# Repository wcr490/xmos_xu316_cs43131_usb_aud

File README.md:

# xmos_xu316_cs43131_usb_aud

## Firmware Compilation Steps

* install xmos xtc tools vscode extension
* clone (https://github.com/youheng7185/sw_usb_audio.git)
* open with vscode, try building
* after getting error from lib_board_support, delete the lib_board_support and clone this (https://github.com/youheng7185/lib_board_support) into that directory
* when build finishes, run ```./pack.sh``` to generate the rom for qspi flash
* flash qspi flash with ```output.bin```

## Reference

* Bric for its cs43131 schematics and init sequence (https://github.com/zephray/Bric)
* Blog by WuXi for cs43131 registers (https://wuxiproj.mzy7.cn/posts/a75c0c32)

## Main Component
* XU316-1024-QF60B-C24
* STMicro USB6B1 USB ESD protection
* Generic USB-C 2.0 TH port
* Winbond W25Q64JVS
* Seiko Epson FA-238 (24 Mhz)
* TI TPS563201 (1.8v dcdc), this requires a 252012 size 2.2uH inductor
* RT9013-33GB, 3.3v ldo
* RT9013-18GB, 1.8v ldo (x4, notes: inside the schematics, 1.8v ldo also uses 3.3v ldo symbol)
* NDK NZ2520SDA-24.576MHZ
* Cirrus Logic CS43131-CNZR
* PJ-327A0-SMT (audio jack)
* TI PCA9306DCUR
* TI SN74AVC4T774PWR
* common values of resistor and capacitor

## Pictures

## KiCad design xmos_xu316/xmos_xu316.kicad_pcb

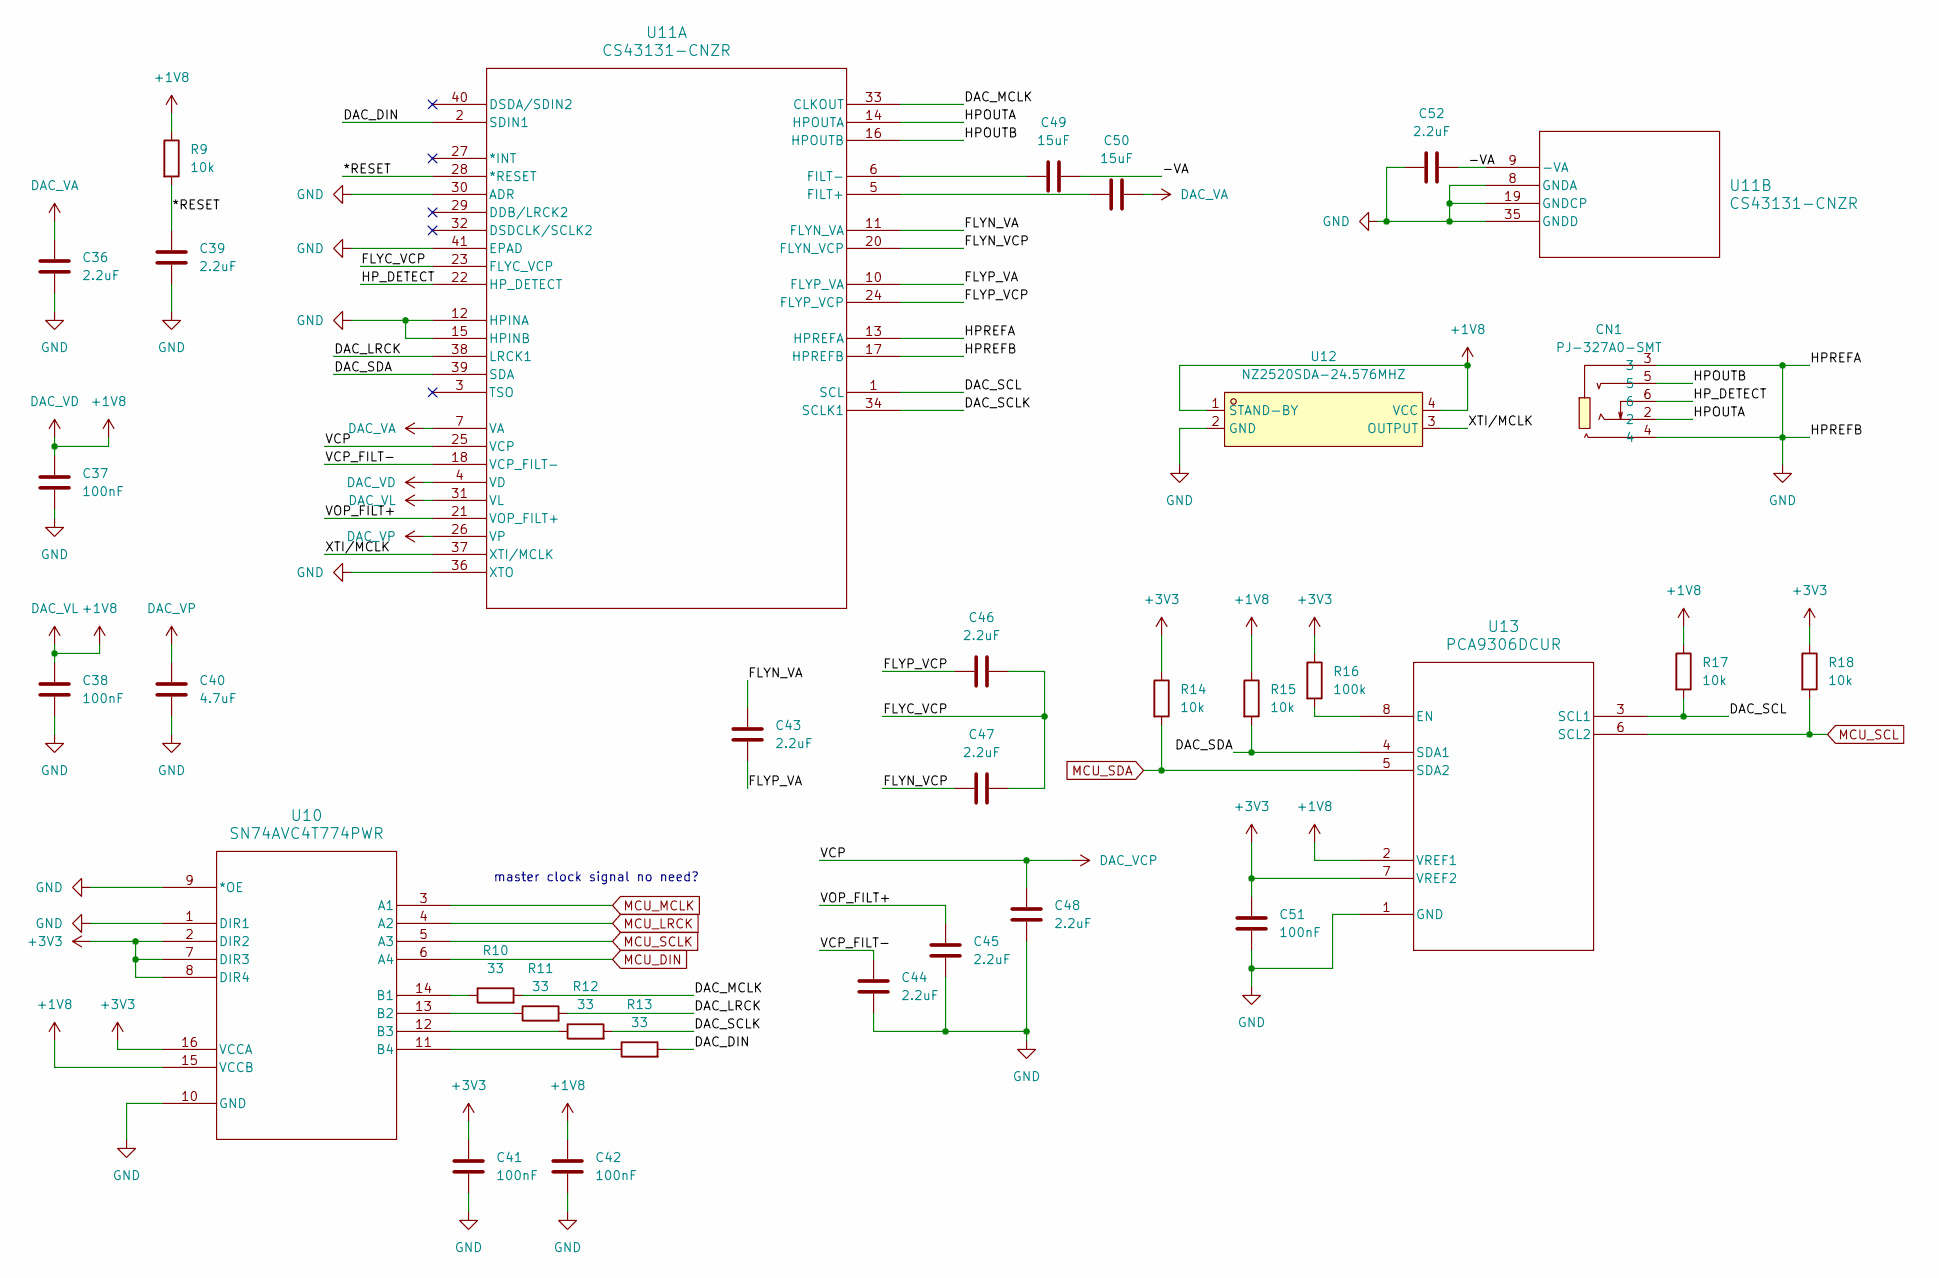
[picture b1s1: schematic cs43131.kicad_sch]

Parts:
C36, C39, C43, C44, C45, C46, C47, C48, C52: 2.2uF; C_0603_1608Metric
C37, C38, C41, C42, C51: 100nF; C_0603_1608Metric
C40: 4.7uF; C_0603_1608Metric
C49, C50: 15uF; C_0603_1608Metric
CN1: PJ-327A0-SMT; AUDIO-SMD_PJ-327A0-SMT; LCSC Part C381135
R9, R14, R15, R17, R18: 10k; R_0603_1608Metric
R10, R11, R12, R13: 33; R_0603_1608Metric
R16: 100k; R_0603_1608Metric
U10: SN74AVC4T774PWR; PW16-M
U11: CS43131-CNZR; QFN40_CS43131-CNZR_CIR-M
U12: NZ2520SDA-24.576MHZ; OSC-SMD_4P-L2.5-W2.0-BL_YSO8008MR; LCSC Part C2846938
U13: PCA9306DCUR; DCU8-M

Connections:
+1V8: C37.1, C38.1, C42.1, R9.1, R15.1, R17.1, U10.15 (VCCB), U11.4 (VD), U11.31 (VL), U12.1 (STAND-BY), U12.4 (VCC), U13.2 (VREF1); also elsewhere on the board
+3V3: C41.1, C51.1, R14.1, R16.1, R18.1, U10.2 (DIR2), U10.7 (DIR3), U10.8 (DIR4), U10.16 (VCCA), U13.7 (VREF2); also elsewhere on the board
/cs43131/*RESET: C39.1, R9.2, U11.28 (*RESET)
/cs43131/-VA: C49.2, C52.2, U11.9 (-VA)
/cs43131/DAC_DIN: R13.2, U11.2 (SDIN1)
/cs43131/DAC_LRCK: R11.2, U11.38 (LRCK1)
/cs43131/DAC_MCLK: R10.2, U11.33 (CLKOUT)
/cs43131/DAC_SCL: R17.2, U11.1 (SCL), U13.3 (SCL1)
/cs43131/DAC_SCLK: R12.2, U11.34 (SCLK1)
/cs43131/DAC_SDA: R15.2, U11.39 (SDA), U13.4 (SDA1)
/cs43131/FLYC_VCP: C46.2, C47.2, U11.23 (FLYC_VCP)
/cs43131/FLYN_VA: C43.1, U11.11 (FLYN_VA)
/cs43131/FLYN_VCP: C47.1, U11.20 (FLYN_VCP)
/cs43131/FLYP_VA: C43.2, U11.10 (FLYP_VA)
/cs43131/FLYP_VCP: C46.1, U11.24 (FLYP_VCP)
/cs43131/HPOUTA: CN1.2, U11.14 (HPOUTA)
/cs43131/HPOUTB: CN1.5, U11.16 (HPOUTB)
/cs43131/HP_DETECT: CN1.6, U11.22 (HP_DETECT)
/cs43131/VCP_FILT-: C44.1, U11.18 (VCP_FILT-)
/cs43131/VOP_FILT+: C45.1, U11.21 (VOP_FILT+)
/cs43131/XTI/MCLK: U11.37 (XTI/MCLK), U12.3 (OUTPUT)
DAC_VA: C36.1, C50.2, U11.7 (VA); also elsewhere on the board
DAC_VCP: C48.1, U11.25 (VCP); also elsewhere on the board
DAC_VP: C40.1, U11.26 (VP); also elsewhere on the board
GND: C36.2, C37.2, C38.2, C39.2, C40.2, C41.2, C42.2, C44.2, C45.2, C48.2, C51.2, C52.1, CN1.3, CN1.4, U10.1 (DIR1), U10.9 (*OE), U10.10 (GND), U11.8 (GNDA), U11.12 (HPINA), U11.13 (HPREFA), U11.15 (HPINB), U11.17 (HPREFB), U11.19 (GNDCP), U11.30 (ADR), U11.35 (GNDD), U11.36 (XTO), U11.41 (EPAD), U12.2 (GND), U13.1 (GND); also elsewhere on the board
MCU_DIN: U10.6 (A4); also elsewhere on the board
MCU_LRCK: U10.4 (A2); also elsewhere on the board
MCU_MCLK: U10.3 (A1); also elsewhere on the board
MCU_SCL: R18.2, U13.6 (SCL2); also elsewhere on the board
MCU_SCLK: U10.5 (A3); also elsewhere on the board
MCU_SDA: R14.2, U13.5 (SDA2); also elsewhere on the board
unnamed: R10.1, U10.14 (B1)
unnamed: R11.1, U10.13 (B2)
unnamed: R12.1, U10.12 (B3)
unnamed: R13.1, U10.11 (B4)
unnamed: C50.1, U11.5 (FILT+)
unnamed: C49.1, U11.6 (FILT-)
unnamed: R16.2, U13.8 (EN)

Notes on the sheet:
master clock signal no need?

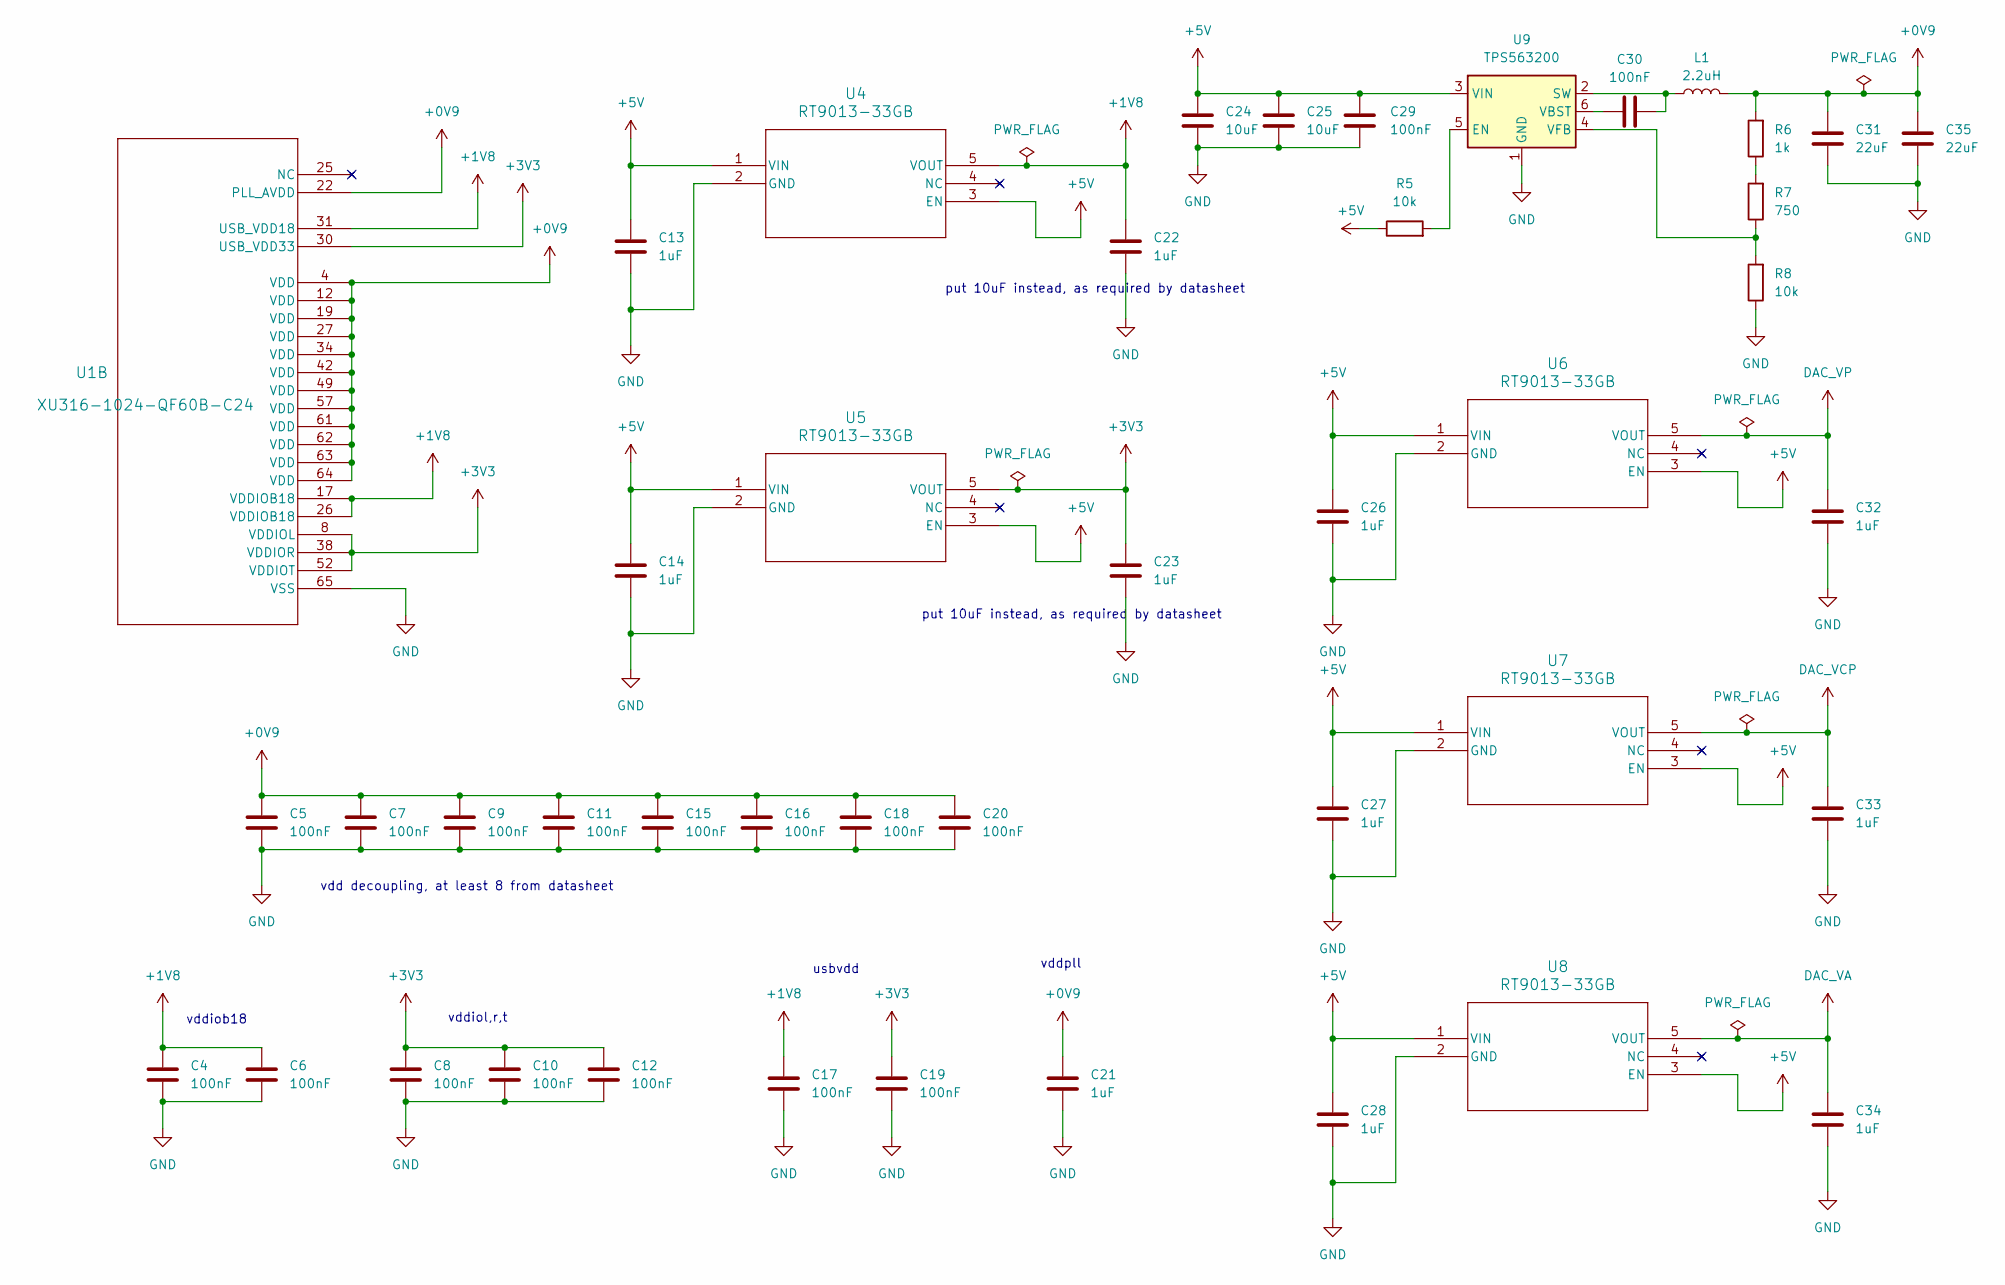
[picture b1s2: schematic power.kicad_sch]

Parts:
C4, C5, C6, C7, C8, C9, C10, C11, C12, C15, C16, C17, C18, C19, C20, C29, C30: 100nF; C_0603_1608Metric
C13, C14, C21, C22, C23, C26, C27, C28, C32, C33, C34: 1uF; C_0603_1608Metric
C24, C25: 10uF; C_0603_1608Metric
C31, C35: 22uF; C_0603_1608Metric
L1: 2.2uH; L_Sunlord_SWPA252012S
R5, R8: 10k; R_0603_1608Metric
R6: 1k; R_0603_1608Metric
R7: 750; R_0603_1608Metric
U1: XU316-1024-QF60B-C24; QFN_F60B-C24_XMO
U4, U5, U6, U7, U8: RT9013-33GB; SOT-23-5_RT9013
U9: TPS563200; SOT-23-6

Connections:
+0V9: C5.1, C7.1, C9.1, C11.1, C15.1, C16.1, C18.1, C20.1, C21.1, C31.1, C35.1, L1.2, R6.2, U1.4 (VDD), U1.12 (VDD), U1.19 (VDD), U1.22 (PLL_AVDD), U1.27 (VDD), U1.34 (VDD), U1.42 (VDD), U1.49 (VDD), U1.57 (VDD), U1.61 (VDD), U1.62 (VDD), U1.63 (VDD), U1.64 (VDD)
+1V8: C4.1, C6.1, C17.1, C22.1, U1.17 (VDDIOB18), U1.26 (VDDIOB18), U1.31 (USB_VDD18), U4.5 (VOUT); also elsewhere on the board
+3V3: C8.1, C10.1, C12.1, C19.1, C23.1, U1.8 (VDDIOL), U1.30 (USB_VDD33), U1.38 (VDDIOR), U1.52 (VDDIOT), U5.5 (VOUT); also elsewhere on the board
+5V: C13.1, C14.1, C24.1, C25.1, C26.1, C27.1, C28.1, C29.2, R5.1, U4.1 (VIN), U4.3 (EN), U5.1 (VIN), U5.3 (EN), U6.1 (VIN), U6.3 (EN), U7.1 (VIN), U7.3 (EN), U8.1 (VIN), U8.3 (EN), U9.3 (VIN); also elsewhere on the board
DAC_VA: C34.1, U8.5 (VOUT); also elsewhere on the board
DAC_VCP: C33.1, U7.5 (VOUT); also elsewhere on the board
DAC_VP: C32.1, U6.5 (VOUT); also elsewhere on the board
GND: C4.2, C5.2, C6.2, C7.2, C8.2, C9.2, C10.2, C11.2, C12.2, C13.2, C14.2, C15.2, C16.2, C17.2, C18.2, C19.2, C20.2, C21.2, C22.2, C23.2, C24.2, C25.2, C26.2, C27.2, C28.2, C29.1, C31.2, C32.2, C33.2, C34.2, C35.2, R8.1, U1.65 (VSS), U4.2 (GND), U5.2 (GND), U6.2 (GND), U7.2 (GND), U8.2 (GND), U9.1 (GND); also elsewhere on the board
unnamed: R6.1, R7.2
unnamed: R5.2, U9.5 (EN)
unnamed: C30.2, L1.1, U9.2 (SW)
unnamed: C30.1, U9.6 (VBST)
unnamed: R7.1, R8.2, U9.4 (VFB)

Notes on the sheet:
vdd decoupling, at least 8 from datasheet
put 10uF instead, as required by datasheet
vddiol,r,t
vddiob18
vddpll
usbvdd

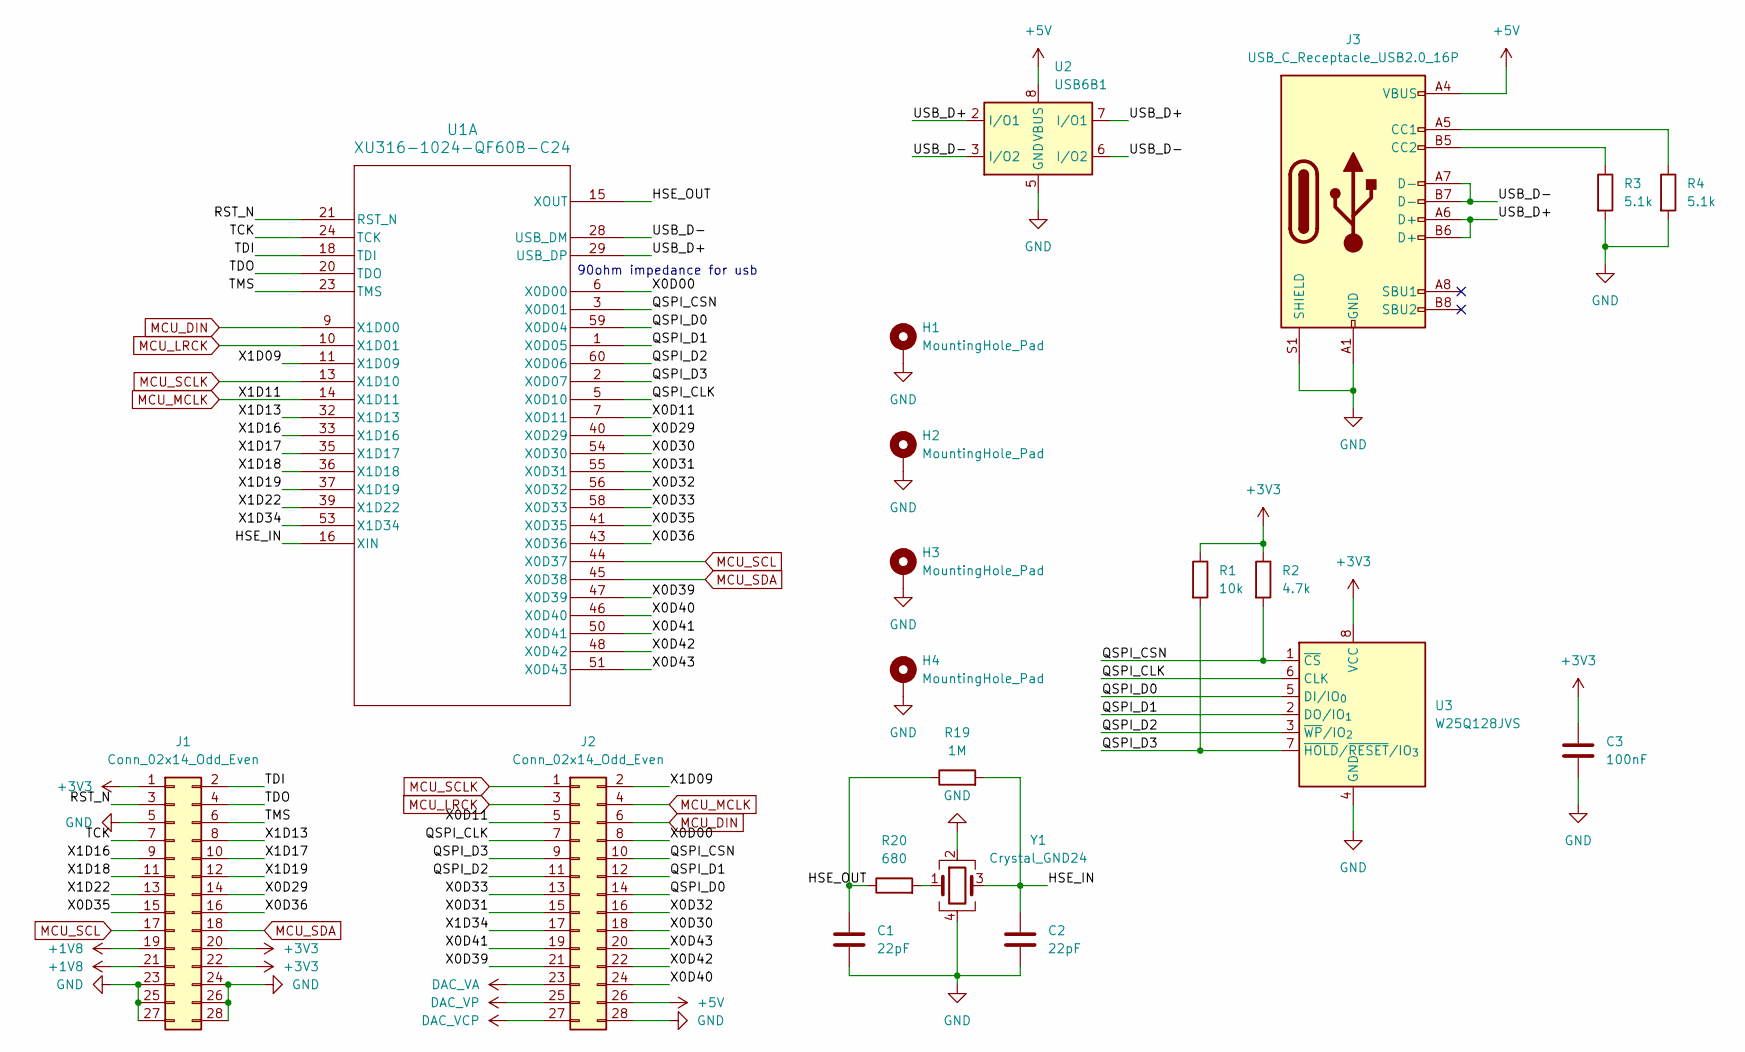
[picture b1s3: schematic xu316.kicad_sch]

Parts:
C1, C2: 22pF; C_0603_1608Metric
C3: 100nF; C_0603_1608Metric
H1, H2, H3, H4: MountingHole_Pad; MountingHole_2.7mm_M2.5_DIN965_Pad_TopBottom
J1, J2: Conn_02x14_Odd_Even; PinHeader_2x14_P2.54mm_Vertical
J3: USB_C_Receptacle_USB2.0_16P; USB_C_Receptacle_GCT_USB4105-xx-A_16P_TopMnt_Horizontal
R1: 10k; R_0603_1608Metric
R2: 4.7k; R_0603_1608Metric
R3, R4: 5.1k; R_0603_1608Metric
R19: 1M; R_0603_1608Metric
R20: 680; R_0603_1608Metric
U1: XU316-1024-QF60B-C24; QFN_F60B-C24_XMO
U2: USB6B1; SOIC-8_3.9x4.9mm_P1.27mm
U3: W25Q128JVS; SOIC-8_5.3x5.3mm_P1.27mm
Y1: Crystal_GND24; Crystal_SMD_3225-4Pin_3.2x2.5mm

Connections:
+1V8: J1.19, J1.21; also elsewhere on the board
+3V3: C3.1, J1.1, J1.20, J1.22, R1.1, R2.1, U3.8 (VCC); also elsewhere on the board
+5V: J2.26, J3.A4 (VBUS), J3.A9 (VBUS), J3.B4 (VBUS), J3.B9 (VBUS), U2.1 (VBUS), U2.8 (VBUS); also elsewhere on the board
/xu316/HSE_IN: C2.1, R19.2, U1.16 (XIN), Y1.3
/xu316/HSE_OUT: C1.1, R19.1, R20.1, U1.15 (XOUT)
/xu316/QSPI_CLK: J2.7, U1.5 (X0D10), U3.6 (CLK)
/xu316/QSPI_CSN: J2.10, R2.2, U1.3 (X0D01), U3.1 (~CS)
/xu316/QSPI_D0: J2.14, U1.59 (X0D04), U3.5 (DI/IO_{0})
/xu316/QSPI_D1: J2.12, U1.1 (X0D05), U3.2 (DO/IO_{1})
/xu316/QSPI_D2: J2.11, U1.60 (X0D06), U3.3 (~WP/IO_{2})
/xu316/QSPI_D3: J2.9, R1.2, U1.2 (X0D07), U3.7 (~HOLD/~RESET/IO_{3})
/xu316/RST_N: J1.3, U1.21 (RST_N)
/xu316/TCK: J1.7, U1.24 (TCK)
/xu316/TDI: J1.2, U1.18 (TDI)
/xu316/TDO: J1.4, U1.20 (TDO)
/xu316/TMS: J1.6, U1.23 (TMS)
/xu316/USB_D+: J3.A6 (D+), J3.B6 (D+), U1.29 (USB_DP), U2.2 (I/O1), U2.7 (I/O1)
/xu316/USB_D-: J3.A7 (D-), J3.B7 (D-), U1.28 (USB_DM), U2.3 (I/O2), U2.6 (I/O2)
/xu316/X0D00: J2.8, U1.6 (X0D00)
/xu316/X0D11: J2.5, U1.7 (X0D11)
/xu316/X0D29: J1.14, U1.40 (X0D29)
/xu316/X0D30: J2.18, U1.54 (X0D30)
/xu316/X0D31: J2.15, U1.55 (X0D31)
/xu316/X0D32: J2.16, U1.56 (X0D32)
/xu316/X0D33: J2.13, U1.58 (X0D33)
/xu316/X0D35: J1.15, U1.41 (X0D35)
/xu316/X0D36: J1.16, U1.43 (X0D36)
/xu316/X0D39: J2.21, U1.47 (X0D39)
/xu316/X0D40: J2.24, U1.46 (X0D40)
/xu316/X0D41: J2.19, U1.50 (X0D41)
/xu316/X0D42: J2.22, U1.48 (X0D42)
/xu316/X0D43: J2.20, U1.51 (X0D43)
/xu316/X1D09: J2.2, U1.11 (X1D09)
/xu316/X1D13: J1.8, U1.32 (X1D13)
/xu316/X1D16: J1.9, U1.33 (X1D16)
/xu316/X1D17: J1.10, U1.35 (X1D17)
/xu316/X1D18: J1.11, U1.36 (X1D18)
/xu316/X1D19: J1.12, U1.37 (X1D19)
/xu316/X1D22: J1.13, U1.39 (X1D22)
/xu316/X1D34: J2.17, U1.53 (X1D34)
DAC_VA: J2.23; also elsewhere on the board
DAC_VCP: J2.27; also elsewhere on the board
DAC_VP: J2.25; also elsewhere on the board
GND: C1.2, C2.2, C3.2, H1.1, H2.1, H3.1, H4.1, J1.5, J1.23, J1.24, J1.25, J1.26, J1.27, J1.28, J2.28, J3.A1 (GND), J3.A12 (GND), J3.B1 (GND), J3.B12 (GND), J3.S1 (SHIELD), R3.2, R4.2, U2.4 (GND), U2.5 (GND), U3.4 (GND), Y1.2, Y1.4; also elsewhere on the board
MCU_DIN: J2.6, U1.9 (X1D00); also elsewhere on the board
MCU_LRCK: J2.3, U1.10 (X1D01); also elsewhere on the board
MCU_MCLK: J2.4, U1.14 (X1D11); also elsewhere on the board
MCU_SCL: J1.17, U1.44 (X0D37); also elsewhere on the board
MCU_SCLK: J2.1, U1.13 (X1D10); also elsewhere on the board
MCU_SDA: J1.18, U1.45 (X0D38); also elsewhere on the board
unnamed: J3.A5 (CC1), R4.1
unnamed: J3.B5 (CC2), R3.1
unnamed: R20.2, Y1.1

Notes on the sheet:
90ohm impedance for usb

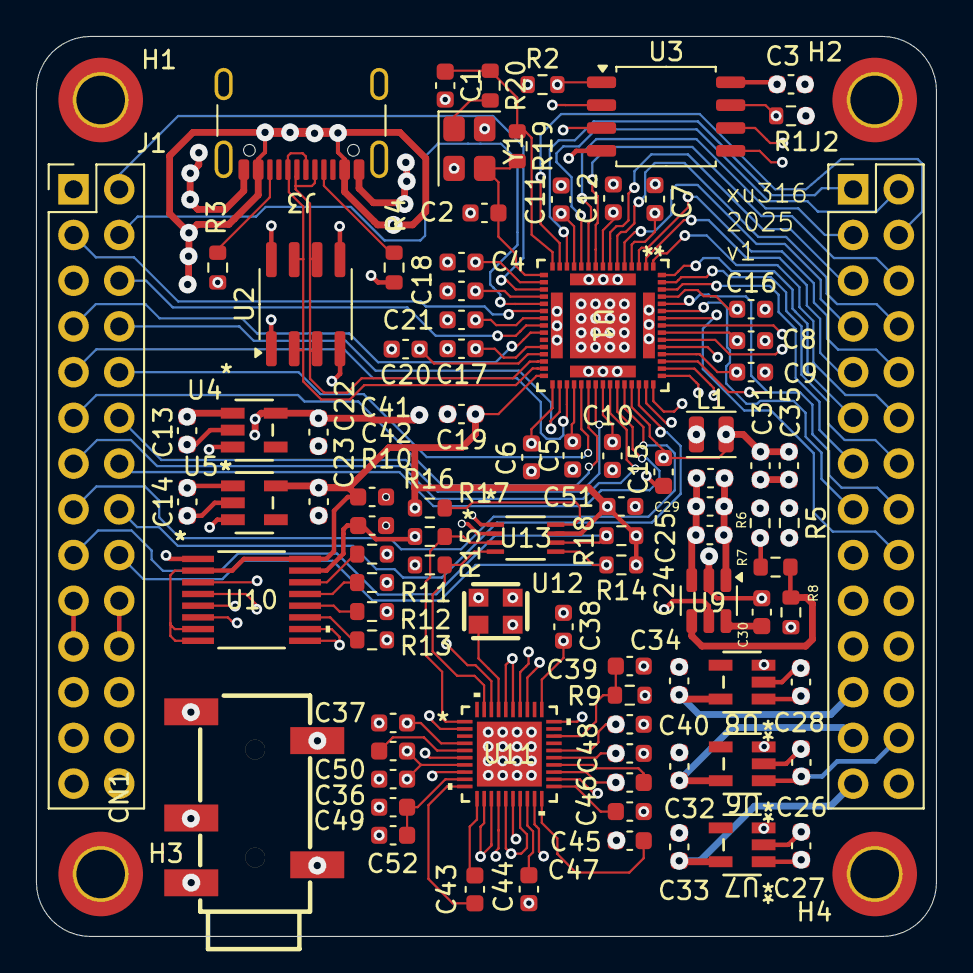
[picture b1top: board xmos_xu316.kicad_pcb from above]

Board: 6 copper layers, 50.0 x 50.0 mm, 95 parts (0 on the bottom side), 85 nets.

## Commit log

2026-04-08 Update README with warnings and compilation steps
    Added warnings and detailed PCB errors and firmware compilation steps.
2026-04-08 add kicad proj
2026-04-08 Update README with reference and components information
    Added references and main component list to README.
2026-04-08 Add pictures section to README
2026-05-03 fixed pcb errors
2026-05-04 fixed one more error(SN74AVC4T774)
2026-05-04 add rd for HSE
